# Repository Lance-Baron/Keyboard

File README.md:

This project is for my own custom keyboard. This project's goal is to learn as much as possible, so I will be trying to do as much as I can myself. So far this includes:
<ul> 
<li>Custom PCB</li>
<li>Custom KeyCaps</li>
<li>Custom Case</li>
<li>Custom Firmware</li>
<li>Custom Stensil</li>
</ul>

Each thing has its own folder, first seperated by folder. 
* ECAD contains all schematics PCB designs, libraies, and 3D models
* CAD contains all 3D models for the Keycaps, the Case, and the Laser Cutting operations
* Code contains all firmware written for the keyboard to work

As there are many subsystems going into this project, there have been a couple of sub projects that have been made to learn about them indivdually first. Bellow you can fine those GitHub Repos.
* [LEDBar](https://github.com/Lance-Baron/LEDBar)

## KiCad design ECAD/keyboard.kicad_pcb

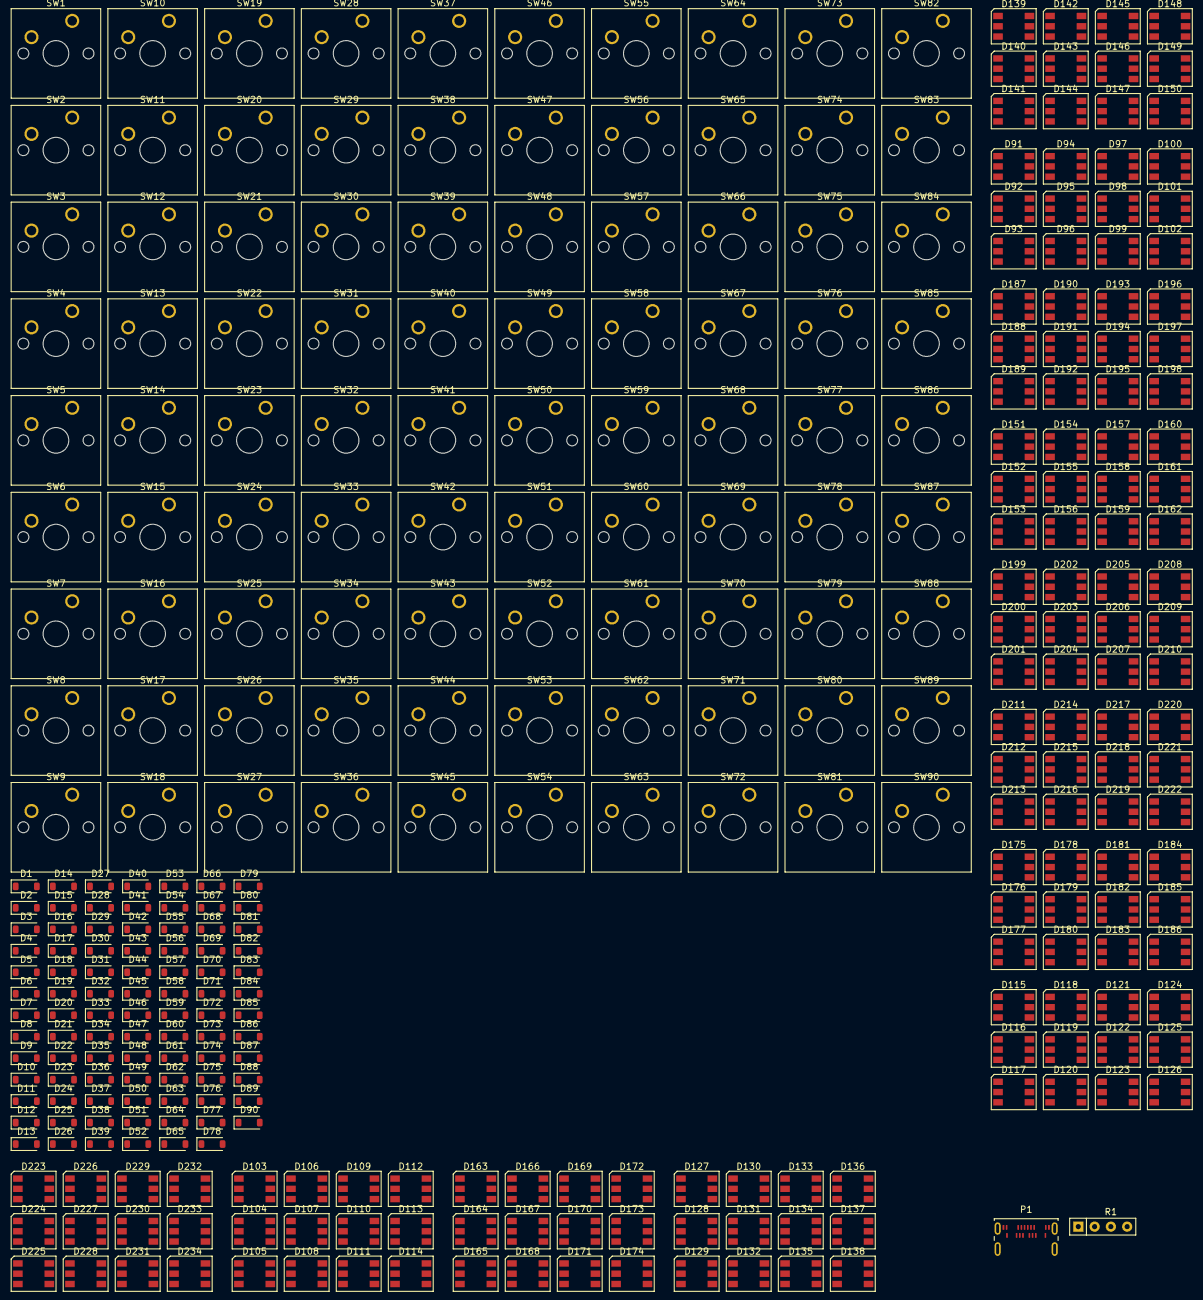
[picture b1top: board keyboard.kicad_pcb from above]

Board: 2 copper layers, 327 parts (0 on the bottom side), 257 nets, no tracks yet.

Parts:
BT1: 3.7 V; Battery_CR1225
D1, D2, D3, D4, D5, D6, D7, D8, D9, D10, D11, D12, D13, D14, D15, D16, D17, D18, D19, D20, D21, D22, D23, D24, D25, D26, D27, D28, D29, D30, D31, D32, D33, D34, D35, D36, D37, D38, D39, D40, D41, D42, D43, D44, D45, D46, D47, D48, D49, D50, D51, D52, D53, D54, D55, D56, D57, D58, D59, D60, D61, D62, D63, D64, D65, D66, D67, D68, D69, D70, D71, D72, D73, D74, D75, D76, D77, D78, D79, D80, D81, D82, D83, D84, D85, D86, D87, D88, D89, D90: 1N4148WT; D_SOD-123
D91, D92, D93, D94, D95, D96, D97, D98, D99, D100, D101, D102, D103, D104, D105, D106, D107, D108, D109, D110, D111, D112, D113, D114, D115, D116, D117, D118, D119, D120, D121, D122, D123, D124, D125, D126, D127, D128, D129, D130, D131, D132, D133, D134, D135, D136, D137, D138, D139, D140, D141, D142, D143, D144, D145, D146, D147, D148, D149, D150, D151, D152, D153, D154, D155, D156, D157, D158, D159, D160, D161, D162, D163, D164, D165, D166, D167, D168, D169, D170, D171, D172, D173, D174, D175, D176, D177, D178, D179, D180, D181, D182, D183, D184, D185, D186, D187, D188, D189, D190, D191, D192, D193, D194, D195, D196, D197, D198, D199, D200, D201, D202, D203, D204, D205, D206, D207, D208, D209, D210, D211, D212, D213, D214, D215, D216, D217, D218, D219, D220, D221, D222, D223, D224, D225, D226, D227, D228, D229, D230, D231, D232, D233, D234: WS2812; LED_WS2812_PLCC6_5.0x5.0mm_P1.6mm
P1: USB_C_Plug_USB2.0; USB_C_Receptacle_Amphenol_124019772112A
R1: 5.1 kOhm; R_Array_SIP4
SW1, SW2, SW3, SW4, SW5, SW6, SW7, SW8, SW9, SW10, SW11, SW12, SW13, SW14, SW15, SW16, SW17, SW18, SW19, SW20, SW21, SW22, SW23, SW24, SW25, SW26, SW27, SW28, SW29, SW30, SW31, SW32, SW33, SW34, SW35, SW36, SW37, SW38, SW39, SW40, SW41, SW42, SW43, SW44, SW45, SW46, SW47, SW48, SW49, SW50, SW51, SW52, SW53, SW54, SW55, SW56, SW57, SW58, SW59, SW60, SW61, SW62, SW63, SW64, SW65, SW66, SW67, SW68, SW69, SW70, SW71, SW72, SW73, SW74, SW75, SW76, SW77, SW78, SW79, SW80, SW81, SW82, SW83, SW84, SW85, SW86, SW87, SW88, SW89, SW90: SW_Push_45deg; SW_Cherry_MX_1.00u_PCB

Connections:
/LEDs/10 LED Array1/LED Data Out: D114.1 (DOUT), D115.2 (DIN)
/LEDs/10 LED Array2/LED Data Out: D126.1 (DOUT), D127.2 (DIN)
/LEDs/10 LED Array3/LED Data Out: D138.1 (DOUT), D139.2 (DIN)
/LEDs/10 LED Array4/LED Data Out: D150.1 (DOUT), D151.2 (DIN)
/LEDs/10 LED Array5/LED Data Out: D162.1 (DOUT), D163.2 (DIN)
/LEDs/10 LED Array6/LED Data Out: D174.1 (DOUT), D175.2 (DIN)
/LEDs/10 LED Array7/LED Data Out: D186.1 (DOUT), D187.2 (DIN)
/LEDs/10 LED Array8/LED Data Out: D198.1 (DOUT), D199.2 (DIN)
/LEDs/10 LED Array10/LED Data In: D210.1 (DOUT), D211.2 (DIN)
/LEDs/10 LED Array10/LED Data Out: D222.1 (DOUT), D223.2 (DIN)
/LEDs/10 LED Array/LED Data Out: D102.1 (DOUT), D103.2 (DIN)
/LEDs/Controller Power: D91.3 (VCC), D92.3 (VCC), D93.3 (VCC), D94.3 (VCC), D95.3 (VCC), D96.3 (VCC), D97.3 (VCC), D98.3 (VCC), D99.3 (VCC), D100.3 (VCC), D101.3 (VCC), D102.3 (VCC), D103.3 (VCC), D104.3 (VCC), D105.3 (VCC), D106.3 (VCC), D107.3 (VCC), D108.3 (VCC), D109.3 (VCC), D110.3 (VCC), D111.3 (VCC), D112.3 (VCC), D113.3 (VCC), D114.3 (VCC), D115.3 (VCC), D116.3 (VCC), D117.3 (VCC), D118.3 (VCC), D119.3 (VCC), D120.3 (VCC), D121.3 (VCC), D122.3 (VCC), D123.3 (VCC), D124.3 (VCC), D125.3 (VCC), D126.3 (VCC), D127.3 (VCC), D128.3 (VCC), D129.3 (VCC), D130.3 (VCC), D131.3 (VCC), D132.3 (VCC), D133.3 (VCC), D134.3 (VCC), D135.3 (VCC), D136.3 (VCC), D137.3 (VCC), D138.3 (VCC), D139.3 (VCC), D140.3 (VCC), D141.3 (VCC), D142.3 (VCC), D143.3 (VCC), D144.3 (VCC), D145.3 (VCC), D146.3 (VCC), D147.3 (VCC), D148.3 (VCC), D149.3 (VCC), D150.3 (VCC), D151.3 (VCC), D152.3 (VCC), D153.3 (VCC), D154.3 (VCC), D155.3 (VCC), D156.3 (VCC), D157.3 (VCC), D158.3 (VCC), D159.3 (VCC), D160.3 (VCC), D161.3 (VCC), D162.3 (VCC), D163.3 (VCC), D164.3 (VCC), D165.3 (VCC), D166.3 (VCC), D167.3 (VCC), D168.3 (VCC), D169.3 (VCC), D170.3 (VCC), D171.3 (VCC), D172.3 (VCC), D173.3 (VCC), D174.3 (VCC), D175.3 (VCC), D176.3 (VCC), D177.3 (VCC), D178.3 (VCC), D179.3 (VCC), D180.3 (VCC), D181.3 (VCC), D182.3 (VCC), D183.3 (VCC), D184.3 (VCC), D185.3 (VCC), D186.3 (VCC), D187.3 (VCC), D188.3 (VCC), D189.3 (VCC), D190.3 (VCC), D191.3 (VCC), D192.3 (VCC), D193.3 (VCC), D194.3 (VCC), D195.3 (VCC), D196.3 (VCC), D197.3 (VCC), D198.3 (VCC), D199.3 (VCC), D200.3 (VCC), D201.3 (VCC), D202.3 (VCC), D203.3 (VCC), D204.3 (VCC), D205.3 (VCC), D206.3 (VCC), D207.3 (VCC), D208.3 (VCC), D209.3 (VCC), D210.3 (VCC), D211.3 (VCC), D212.3 (VCC), D213.3 (VCC), D214.3 (VCC), D215.3 (VCC), D216.3 (VCC), D217.3 (VCC), D218.3 (VCC), D219.3 (VCC), D220.3 (VCC), D221.3 (VCC), D222.3 (VCC), D223.3 (VCC), D224.3 (VCC), D225.3 (VCC), D226.3 (VCC), D227.3 (VCC), D228.3 (VCC), D229.3 (VCC), D230.3 (VCC), D231.3 (VCC), D232.3 (VCC), D233.3 (VCC), D234.3 (VCC)
/LEDs/LED Power: D91.5 (VDD), D92.5 (VDD), D93.5 (VDD), D94.5 (VDD), D95.5 (VDD), D96.5 (VDD), D97.5 (VDD), D98.5 (VDD), D99.5 (VDD), D100.5 (VDD), D101.5 (VDD), D102.5 (VDD), D103.5 (VDD), D104.5 (VDD), D105.5 (VDD), D106.5 (VDD), D107.5 (VDD), D108.5 (VDD), D109.5 (VDD), D110.5 (VDD), D111.5 (VDD), D112.5 (VDD), D113.5 (VDD), D114.5 (VDD), D115.5 (VDD), D116.5 (VDD), D117.5 (VDD), D118.5 (VDD), D119.5 (VDD), D120.5 (VDD), D121.5 (VDD), D122.5 (VDD), D123.5 (VDD), D124.5 (VDD), D125.5 (VDD), D126.5 (VDD), D127.5 (VDD), D128.5 (VDD), D129.5 (VDD), D130.5 (VDD), D131.5 (VDD), D132.5 (VDD), D133.5 (VDD), D134.5 (VDD), D135.5 (VDD), D136.5 (VDD), D137.5 (VDD), D138.5 (VDD), D139.5 (VDD), D140.5 (VDD), D141.5 (VDD), D142.5 (VDD), D143.5 (VDD), D144.5 (VDD), D145.5 (VDD), D146.5 (VDD), D147.5 (VDD), D148.5 (VDD), D149.5 (VDD), D150.5 (VDD), D151.5 (VDD), D152.5 (VDD), D153.5 (VDD), D154.5 (VDD), D155.5 (VDD), D156.5 (VDD), D157.5 (VDD), D158.5 (VDD), D159.5 (VDD), D160.5 (VDD), D161.5 (VDD), D162.5 (VDD), D163.5 (VDD), D164.5 (VDD), D165.5 (VDD), D166.5 (VDD), D167.5 (VDD), D168.5 (VDD), D169.5 (VDD), D170.5 (VDD), D171.5 (VDD), D172.5 (VDD), D173.5 (VDD), D174.5 (VDD), D175.5 (VDD), D176.5 (VDD), D177.5 (VDD), D178.5 (VDD), D179.5 (VDD), D180.5 (VDD), D181.5 (VDD), D182.5 (VDD), D183.5 (VDD), D184.5 (VDD), D185.5 (VDD), D186.5 (VDD), D187.5 (VDD), D188.5 (VDD), D189.5 (VDD), D190.5 (VDD), D191.5 (VDD), D192.5 (VDD), D193.5 (VDD), D194.5 (VDD), D195.5 (VDD), D196.5 (VDD), D197.5 (VDD), D198.5 (VDD), D199.5 (VDD), D200.5 (VDD), D201.5 (VDD), D202.5 (VDD), D203.5 (VDD), D204.5 (VDD), D205.5 (VDD), D206.5 (VDD), D207.5 (VDD), D208.5 (VDD), D209.5 (VDD), D210.5 (VDD), D211.5 (VDD), D212.5 (VDD), D213.5 (VDD), D214.5 (VDD), D215.5 (VDD), D216.5 (VDD), D217.5 (VDD), D218.5 (VDD), D219.5 (VDD), D220.5 (VDD), D221.5 (VDD), D222.5 (VDD), D223.5 (VDD), D224.5 (VDD), D225.5 (VDD), D226.5 (VDD), D227.5 (VDD), D228.5 (VDD), D229.5 (VDD), D230.5 (VDD), D231.5 (VDD), D232.5 (VDD), D233.5 (VDD), D234.5 (VDD)
Col0: SW9.1, SW18.1, SW35.1, SW36.1, SW69.1, SW70.1, SW71.1, SW72.1, SW89.1, SW90.1
Col1: SW8.1, SW17.1, SW33.1, SW34.1, SW65.1, SW66.1, SW67.1, SW68.1, SW87.1, SW88.1
Col2: SW7.1, SW16.1, SW31.1, SW32.1, SW61.1, SW62.1, SW63.1, SW64.1, SW85.1, SW86.1
Col3: SW6.1, SW15.1, SW29.1, SW30.1, SW57.1, SW58.1, SW59.1, SW60.1, SW83.1, SW84.1
Col4: SW5.1, SW14.1, SW27.1, SW28.1, SW53.1, SW54.1, SW55.1, SW56.1, SW81.1, SW82.1
Col5: SW4.1, SW13.1, SW25.1, SW26.1, SW49.1, SW50.1, SW51.1, SW52.1, SW79.1, SW80.1
Col6: SW3.1, SW12.1, SW23.1, SW24.1, SW45.1, SW46.1, SW47.1, SW48.1, SW77.1, SW78.1
Col7: SW2.1, SW11.1, SW21.1, SW22.1, SW41.1, SW42.1, SW43.1, SW44.1, SW75.1, SW76.1
Col8: SW1.1, SW10.1, SW19.1, SW20.1, SW37.1, SW38.1, SW39.1, SW40.1, SW73.1, SW74.1
GND: D91.6 (VSS), D92.6 (VSS), D93.6 (VSS), D94.6 (VSS), D95.6 (VSS), D96.6 (VSS), D97.6 (VSS), D98.6 (VSS), D99.6 (VSS), D100.6 (VSS), D101.6 (VSS), D102.6 (VSS), D103.6 (VSS), D104.6 (VSS), D105.6 (VSS), D106.6 (VSS), D107.6 (VSS), D108.6 (VSS), D109.6 (VSS), D110.6 (VSS), D111.6 (VSS), D112.6 (VSS), D113.6 (VSS), D114.6 (VSS), D115.6 (VSS), D116.6 (VSS), D117.6 (VSS), D118.6 (VSS), D119.6 (VSS), D120.6 (VSS), D121.6 (VSS), D122.6 (VSS), D123.6 (VSS), D124.6 (VSS), D125.6 (VSS), D126.6 (VSS), D127.6 (VSS), D128.6 (VSS), D129.6 (VSS), D130.6 (VSS), D131.6 (VSS), D132.6 (VSS), D133.6 (VSS), D134.6 (VSS), D135.6 (VSS), D136.6 (VSS), D137.6 (VSS), D138.6 (VSS), D139.6 (VSS), D140.6 (VSS), D141.6 (VSS), D142.6 (VSS), D143.6 (VSS), D144.6 (VSS), D145.6 (VSS), D146.6 (VSS), D147.6 (VSS), D148.6 (VSS), D149.6 (VSS), D150.6 (VSS), D151.6 (VSS), D152.6 (VSS), D153.6 (VSS), D154.6 (VSS), D155.6 (VSS), D156.6 (VSS), D157.6 (VSS), D158.6 (VSS), D159.6 (VSS), D160.6 (VSS), D161.6 (VSS), D162.6 (VSS), D163.6 (VSS), D164.6 (VSS), D165.6 (VSS), D166.6 (VSS), D167.6 (VSS), D168.6 (VSS), D169.6 (VSS), D170.6 (VSS), D171.6 (VSS), D172.6 (VSS), D173.6 (VSS), D174.6 (VSS), D175.6 (VSS), D176.6 (VSS), D177.6 (VSS), D178.6 (VSS), D179.6 (VSS), D180.6 (VSS), D181.6 (VSS), D182.6 (VSS), D183.6 (VSS), D184.6 (VSS), D185.6 (VSS), D186.6 (VSS), D187.6 (VSS), D188.6 (VSS), D189.6 (VSS), D190.6 (VSS), D191.6 (VSS), D192.6 (VSS), D193.6 (VSS), D194.6 (VSS), D195.6 (VSS), D196.6 (VSS), D197.6 (VSS), D198.6 (VSS), D199.6 (VSS), D200.6 (VSS), D201.6 (VSS), D202.6 (VSS), D203.6 (VSS), D204.6 (VSS), D205.6 (VSS), D206.6 (VSS), D207.6 (VSS), D208.6 (VSS), D209.6 (VSS), D210.6 (VSS), D211.6 (VSS), D212.6 (VSS), D213.6 (VSS), D214.6 (VSS), D215.6 (VSS), D216.6 (VSS), D217.6 (VSS), D218.6 (VSS), D219.6 (VSS), D220.6 (VSS), D221.6 (VSS), D222.6 (VSS), D223.6 (VSS), D224.6 (VSS), D225.6 (VSS), D226.6 (VSS), D227.6 (VSS), D228.6 (VSS), D229.6 (VSS), D230.6 (VSS), D231.6 (VSS), D232.6 (VSS), D233.6 (VSS), D234.1 (DOUT), D234.6 (VSS), P1.A1 (GND), P1.A12 (GND), P1.B1 (GND), P1.B5 (VCONN), P1.B12 (GND), P1.S1 (SHIELD), R1.1
unnamed: P1.A4 (VBUS), P1.A9 (VBUS), P1.B4 (VBUS), P1.B9 (VBUS)
unnamed: D1.2 (A), SW1.2
unnamed: D2.2 (A), SW2.2
unnamed: D3.2 (A), SW3.2
unnamed: D4.2 (A), SW4.2
unnamed: D5.2 (A), SW5.2
unnamed: D6.2 (A), SW6.2
unnamed: D7.2 (A), SW7.2
unnamed: D8.2 (A), SW8.2
unnamed: D9.2 (A), SW9.2
unnamed: D10.2 (A), SW10.2
unnamed: D11.2 (A), SW11.2
unnamed: D12.2 (A), SW12.2
unnamed: D13.2 (A), SW13.2
unnamed: D14.2 (A), SW14.2
unnamed: D15.2 (A), SW15.2
unnamed: D16.2 (A), SW16.2
unnamed: D17.2 (A), SW17.2
unnamed: D18.2 (A), SW18.2
unnamed: D19.2 (A), SW19.2
unnamed: D20.2 (A), SW20.2
unnamed: D21.2 (A), SW21.2
unnamed: D22.2 (A), SW22.2
unnamed: D23.2 (A), SW23.2
unnamed: D24.2 (A), SW24.2
unnamed: D25.2 (A), SW25.2
unnamed: D26.2 (A), SW26.2
unnamed: D27.2 (A), SW27.2
unnamed: D28.2 (A), SW28.2
unnamed: D29.2 (A), SW29.2
unnamed: D30.2 (A), SW30.2
unnamed: D31.2 (A), SW31.2
unnamed: D32.2 (A), SW32.2
unnamed: D33.2 (A), SW33.2
unnamed: D34.2 (A), SW34.2
unnamed: D35.2 (A), SW35.2
unnamed: D36.2 (A), SW36.2
unnamed: D37.2 (A), SW37.2
unnamed: D38.2 (A), SW38.2
unnamed: D39.2 (A), SW39.2
unnamed: D40.2 (A), SW40.2
unnamed: D41.2 (A), SW41.2
unnamed: D42.2 (A), SW42.2
unnamed: D43.2 (A), SW43.2
unnamed: D44.2 (A), SW44.2
unnamed: D45.2 (A), SW45.2
unnamed: D46.2 (A), SW46.2
unnamed: D47.2 (A), SW47.2
unnamed: D48.2 (A), SW48.2
unnamed: D49.2 (A), SW49.2
unnamed: D50.2 (A), SW50.2
unnamed: D51.2 (A), SW51.2
unnamed: D52.2 (A), SW52.2
unnamed: D53.2 (A), SW53.2
unnamed: D54.2 (A), SW54.2
unnamed: D55.2 (A), SW55.2
unnamed: D56.2 (A), SW56.2
unnamed: D57.2 (A), SW57.2
unnamed: D58.2 (A), SW58.2
unnamed: D59.2 (A), SW59.2
unnamed: D60.2 (A), SW60.2
unnamed: D61.2 (A), SW61.2
unnamed: D62.2 (A), SW62.2
unnamed: D63.2 (A), SW63.2
unnamed: D64.2 (A), SW64.2
unnamed: D65.2 (A), SW65.2
unnamed: D66.2 (A), SW66.2
unnamed: D67.2 (A), SW67.2
unnamed: D68.2 (A), SW68.2
unnamed: D69.2 (A), SW69.2
unnamed: D70.2 (A), SW70.2
unnamed: D71.2 (A), SW71.2
unnamed: D72.2 (A), SW72.2
unnamed: D73.2 (A), SW73.2
unnamed: D74.2 (A), SW74.2
unnamed: D75.2 (A), SW75.2
unnamed: D76.2 (A), SW76.2
unnamed: D77.2 (A), SW77.2
unnamed: D78.2 (A), SW78.2
unnamed: D79.2 (A), SW79.2
unnamed: D80.2 (A), SW80.2
unnamed: D81.2 (A), SW81.2
unnamed: D82.2 (A), SW82.2
unnamed: D83.2 (A), SW83.2
unnamed: D84.2 (A), SW84.2
unnamed: D85.2 (A), SW85.2
unnamed: D86.2 (A), SW86.2
unnamed: D87.2 (A), SW87.2
unnamed: D88.2 (A), SW88.2
unnamed: D89.2 (A), SW89.2
unnamed: D90.2 (A), SW90.2
unnamed: D91.1 (DOUT), D92.2 (DIN)
unnamed: D92.1 (DOUT), D93.2 (DIN)
unnamed: D93.1 (DOUT), D94.2 (DIN)
unnamed: D94.1 (DOUT), D95.2 (DIN)
unnamed: D95.1 (DOUT), D96.2 (DIN)
unnamed: D96.1 (DOUT), D97.2 (DIN)
unnamed: D97.1 (DOUT), D98.2 (DIN)
unnamed: D98.1 (DOUT), D99.2 (DIN)
unnamed: D99.1 (DOUT), D100.2 (DIN)
unnamed: D100.1 (DOUT), D101.2 (DIN)
unnamed: D101.1 (DOUT), D102.2 (DIN)
unnamed: D103.1 (DOUT), D104.2 (DIN)
unnamed: D104.1 (DOUT), D105.2 (DIN)
unnamed: D105.1 (DOUT), D106.2 (DIN)
unnamed: D106.1 (DOUT), D107.2 (DIN)
unnamed: D107.1 (DOUT), D108.2 (DIN)
unnamed: D108.1 (DOUT), D109.2 (DIN)
unnamed: D109.1 (DOUT), D110.2 (DIN)
unnamed: D110.1 (DOUT), D111.2 (DIN)
unnamed: D111.1 (DOUT), D112.2 (DIN)
unnamed: D112.1 (DOUT), D113.2 (DIN)
unnamed: D113.1 (DOUT), D114.2 (DIN)
unnamed: D115.1 (DOUT), D116.2 (DIN)
unnamed: D116.1 (DOUT), D117.2 (DIN)
unnamed: D117.1 (DOUT), D118.2 (DIN)
unnamed: D118.1 (DOUT), D119.2 (DIN)
unnamed: D119.1 (DOUT), D120.2 (DIN)
unnamed: D120.1 (DOUT), D121.2 (DIN)
unnamed: D121.1 (DOUT), D122.2 (DIN)
unnamed: D122.1 (DOUT), D123.2 (DIN)
unnamed: D123.1 (DOUT), D124.2 (DIN)
unnamed: D124.1 (DOUT), D125.2 (DIN)
unnamed: D125.1 (DOUT), D126.2 (DIN)
unnamed: D127.1 (DOUT), D128.2 (DIN)
unnamed: D128.1 (DOUT), D129.2 (DIN)
unnamed: D129.1 (DOUT), D130.2 (DIN)
unnamed: D130.1 (DOUT), D131.2 (DIN)
unnamed: D131.1 (DOUT), D132.2 (DIN)
unnamed: D132.1 (DOUT), D133.2 (DIN)
unnamed: D133.1 (DOUT), D134.2 (DIN)
unnamed: D134.1 (DOUT), D135.2 (DIN)
unnamed: D135.1 (DOUT), D136.2 (DIN)
unnamed: D136.1 (DOUT), D137.2 (DIN)
unnamed: D137.1 (DOUT), D138.2 (DIN)
unnamed: D139.1 (DOUT), D140.2 (DIN)
unnamed: D140.1 (DOUT), D141.2 (DIN)
unnamed: D141.1 (DOUT), D142.2 (DIN)
unnamed: D142.1 (DOUT), D143.2 (DIN)
unnamed: D143.1 (DOUT), D144.2 (DIN)
unnamed: D144.1 (DOUT), D145.2 (DIN)
unnamed: D145.1 (DOUT), D146.2 (DIN)
unnamed: D146.1 (DOUT), D147.2 (DIN)
unnamed: D147.1 (DOUT), D148.2 (DIN)
unnamed: D148.1 (DOUT), D149.2 (DIN)
unnamed: D149.1 (DOUT), D150.2 (DIN)
unnamed: D151.1 (DOUT), D152.2 (DIN)
unnamed: D152.1 (DOUT), D153.2 (DIN)
unnamed: D153.1 (DOUT), D154.2 (DIN)
unnamed: D154.1 (DOUT), D155.2 (DIN)
unnamed: D155.1 (DOUT), D156.2 (DIN)
unnamed: D156.1 (DOUT), D157.2 (DIN)
unnamed: D157.1 (DOUT), D158.2 (DIN)
unnamed: D158.1 (DOUT), D159.2 (DIN)
unnamed: D159.1 (DOUT), D160.2 (DIN)
unnamed: D160.1 (DOUT), D161.2 (DIN)
unnamed: D161.1 (DOUT), D162.2 (DIN)
unnamed: D163.1 (DOUT), D164.2 (DIN)
unnamed: D164.1 (DOUT), D165.2 (DIN)
unnamed: D165.1 (DOUT), D166.2 (DIN)
unnamed: D166.1 (DOUT), D167.2 (DIN)
unnamed: D167.1 (DOUT), D168.2 (DIN)
unnamed: D168.1 (DOUT), D169.2 (DIN)
unnamed: D169.1 (DOUT), D170.2 (DIN)
unnamed: D170.1 (DOUT), D171.2 (DIN)
unnamed: D171.1 (DOUT), D172.2 (DIN)
unnamed: D172.1 (DOUT), D173.2 (DIN)
unnamed: D173.1 (DOUT), D174.2 (DIN)
unnamed: D175.1 (DOUT), D176.2 (DIN)
unnamed: D176.1 (DOUT), D177.2 (DIN)
unnamed: D177.1 (DOUT), D178.2 (DIN)
unnamed: D178.1 (DOUT), D179.2 (DIN)
unnamed: D179.1 (DOUT), D180.2 (DIN)
unnamed: D180.1 (DOUT), D181.2 (DIN)
unnamed: D181.1 (DOUT), D182.2 (DIN)
unnamed: D182.1 (DOUT), D183.2 (DIN)
unnamed: D183.1 (DOUT), D184.2 (DIN)
unnamed: D184.1 (DOUT), D185.2 (DIN)
unnamed: D185.1 (DOUT), D186.2 (DIN)
unnamed: D187.1 (DOUT), D188.2 (DIN)
unnamed: D188.1 (DOUT), D189.2 (DIN)
unnamed: D189.1 (DOUT), D190.2 (DIN)
unnamed: D190.1 (DOUT), D191.2 (DIN)
unnamed: D191.1 (DOUT), D192.2 (DIN)
unnamed: D192.1 (DOUT), D193.2 (DIN)
unnamed: D193.1 (DOUT), D194.2 (DIN)
unnamed: D194.1 (DOUT), D195.2 (DIN)
unnamed: D195.1 (DOUT), D196.2 (DIN)
unnamed: D196.1 (DOUT), D197.2 (DIN)
unnamed: D197.1 (DOUT), D198.2 (DIN)
unnamed: D199.1 (DOUT), D200.2 (DIN)
unnamed: D200.1 (DOUT), D201.2 (DIN)
unnamed: D201.1 (DOUT), D202.2 (DIN)
unnamed: D202.1 (DOUT), D203.2 (DIN)
unnamed: D203.1 (DOUT), D204.2 (DIN)
unnamed: D204.1 (DOUT), D205.2 (DIN)
unnamed: D205.1 (DOUT), D206.2 (DIN)
unnamed: D206.1 (DOUT), D207.2 (DIN)
unnamed: D207.1 (DOUT), D208.2 (DIN)
unnamed: D208.1 (DOUT), D209.2 (DIN)
unnamed: D209.1 (DOUT), D210.2 (DIN)
unnamed: D211.1 (DOUT), D212.2 (DIN)
unnamed: D212.1 (DOUT), D213.2 (DIN)
unnamed: D213.1 (DOUT), D214.2 (DIN)
unnamed: D214.1 (DOUT), D215.2 (DIN)
unnamed: D215.1 (DOUT), D216.2 (DIN)
unnamed: D216.1 (DOUT), D217.2 (DIN)
unnamed: D217.1 (DOUT), D218.2 (DIN)
unnamed: D218.1 (DOUT), D219.2 (DIN)
unnamed: D219.1 (DOUT), D220.2 (DIN)
unnamed: D220.1 (DOUT), D221.2 (DIN)
unnamed: D221.1 (DOUT), D222.2 (DIN)
unnamed: D223.1 (DOUT), D224.2 (DIN)
unnamed: D224.1 (DOUT), D225.2 (DIN)
unnamed: D225.1 (DOUT), D226.2 (DIN)
unnamed: D226.1 (DOUT), D227.2 (DIN)
unnamed: D227.1 (DOUT), D228.2 (DIN)
unnamed: D228.1 (DOUT), D229.2 (DIN)
unnamed: D229.1 (DOUT), D230.2 (DIN)
unnamed: D230.1 (DOUT), D231.2 (DIN)
unnamed: D231.1 (DOUT), D232.2 (DIN)
unnamed: D232.1 (DOUT), D233.2 (DIN)
unnamed: D233.1 (DOUT), D234.2 (DIN)
unnamed: P1.A5 (CC), R1.2
Row0: D74.1 (K), D76.1 (K), D78.1 (K), D80.1 (K), D82.1 (K), D84.1 (K), D86.1 (K), D88.1 (K), D90.1 (K)
Row1: D73.1 (K), D75.1 (K), D77.1 (K), D79.1 (K), D81.1 (K), D83.1 (K), D85.1 (K), D87.1 (K), D89.1 (K)
Row2: D40.1 (K), D44.1 (K), D48.1 (K), D52.1 (K), D56.1 (K), D60.1 (K), D64.1 (K), D68.1 (K), D72.1 (K)
Row3: D39.1 (K), D43.1 (K), D47.1 (K), D51.1 (K), D55.1 (K), D59.1 (K), D63.1 (K), D67.1 (K), D71.1 (K)
Row4: D38.1 (K), D42.1 (K), D46.1 (K), D50.1 (K), D54.1 (K), D58.1 (K), D62.1 (K), D66.1 (K), D70.1 (K)
Row5: D37.1 (K), D41.1 (K), D45.1 (K), D49.1 (K), D53.1 (K), D57.1 (K), D61.1 (K), D65.1 (K), D69.1 (K)
Row6: D20.1 (K), D22.1 (K), D24.1 (K), D26.1 (K), D28.1 (K), D30.1 (K), D32.1 (K), D34.1 (K), D36.1 (K)
Row7: D19.1 (K), D21.1 (K), D23.1 (K), D25.1 (K), D27.1 (K), D29.1 (K), D31.1 (K), D33.1 (K), D35.1 (K)
Row8: D10.1 (K), D11.1 (K), D12.1 (K), D13.1 (K), D14.1 (K), D15.1 (K), D16.1 (K), D17.1 (K), D18.1 (K)
Row9: D1.1 (K), D2.1 (K), D3.1 (K), D4.1 (K), D5.1 (K), D6.1 (K), D7.1 (K), D8.1 (K), D9.1 (K)

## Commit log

2026-02-20 Initial .gitignore
2026-02-20 Added KiCad files
2026-02-20 Added README.md
2026-02-20 Added a README to the CAD folder
2026-02-20 Added README.
2026-04-13 Updated Schematic
2026-04-13 Added SubProject Link
